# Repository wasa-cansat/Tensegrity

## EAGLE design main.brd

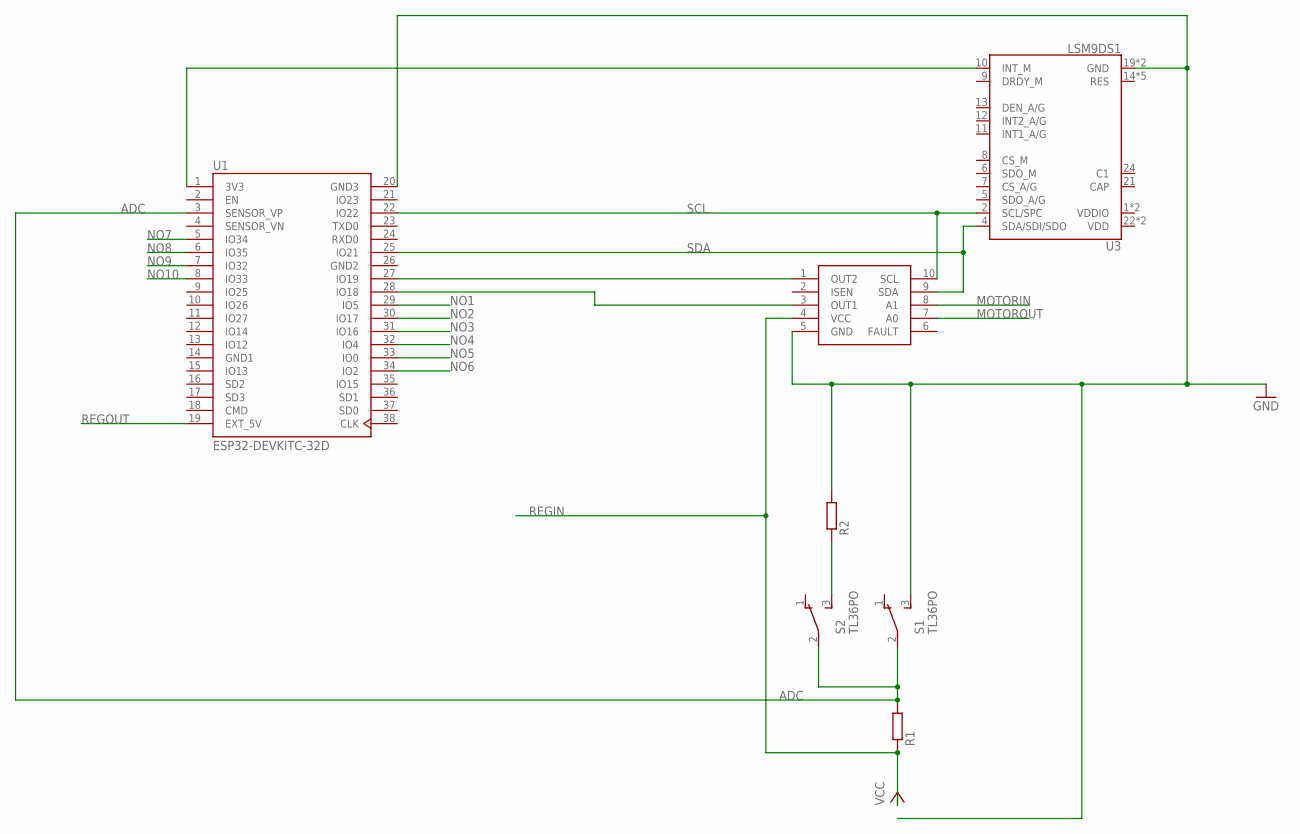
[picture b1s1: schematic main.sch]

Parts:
R1, R2: R-EU_0207/10; 0207/10
S1, S2: TL36PO; TL3XPO
U1: ESP32-DEVKITC-32D; MODULE_ESP32-DEVKITC-32D
U3: LSM9DS1; LGA24-8X4
U$2: DRV8830

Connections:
ADC: R1.2, S1.2, S2.2, U1.3 (SENSOR_VP)
GND: R2.2, S1.3 (S), U1.20 (GND3), U3.19 (GND), U3.20 (GND), U$2.5 (GND)
GND1: U1.14 (GND1)
GND2: U1.26 (GND2)
MOTORIN: U$2.8 (A1)
MOTOROUT: U$2.7 (A0)
unnamed: U1.27 (IO19), U$2.1 (OUT2)
unnamed: U1.28 (IO18), U$2.3 (OUT1)
unnamed: R2.1, S2.3 (S)
unnamed: U1.1 (3V3), U3.10 (INT_M)
NO1: U1.29 (IO5)
NO2: U1.30 (IO17)
NO3: U1.31 (IO16)
NO4: U1.32 (IO4)
NO5: U1.33 (IO0)
NO6: U1.34 (IO2)
NO7: U1.5 (IO34)
NO8: U1.6 (IO35)
NO9: U1.7 (IO32)
NO10: U1.8 (IO33)
REGIN: R1.1, U$2.4 (VCC)
REGOUT: U1.19 (EXT_5V)
SCL: U1.22 (IO22), U3.2 (SCL/SPC), U$2.10 (SCL)
SDA: U1.25 (IO21), U3.4 (SDA/SDI/SDO), U$2.9 (SDA)

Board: 2 copper layers, 7 parts (0 on the bottom side), 9 nets, no tracks yet.

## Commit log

2021-05-06 Init
2021-05-06 yes!
2021-05-09 madatotyuu
2021-05-10 nice!
2021-05-15 Good?
2021-05-15 no message
2021-05-21 Fix gitignore
2021-05-21 Add arduino program
2021-05-21 Move file
2021-05-24 dou?
2021-06-24 What?
2021-10-15 Add limit switch wiring
2021-10-15 Program files
2021-10-17 Start making telemeter
2021-10-21 Showing tensegrity model, parse telemetry
2021-10-22 Message parser, reading & writing data file
2021-10-23 Add timeline
2021-10-26 Fix IMU
2021-10-27 Sending command via telemeter
